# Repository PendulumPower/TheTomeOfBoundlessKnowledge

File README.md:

# The Tome Of Boundless Knowledge
A voice recognition E-paper spell tome and reference book for things such as dnd.
<br>The Tome will listen for a wake word followed by a category of spell, at which point it lists all spells in that category. When one is spoken, it will display it.
<br>I wanted to make this as an easier way to manage spells and other data for these scenerios, and plan to expand it's database past spells in the future and provide alternate firmware for purposes such as just using it as an e-reader.
Here is the full CAD model:

Front and back of the PCB:

And here is the schematic for the design:

Cost Breakdown:<br>
$35 for items in digikey BOM plus shipping, tariffs, and tax <br>
$16 for PCB with PCB, stencil, shipping, and tax <br>
$100 for e-paper display, extra cable, battery, and micro-sd card
$30 for enclosure and assembly costs (filament, more solder, and outer case materials<br>
Amazon list: <a href="https://www.amazon.com/hz/wishlist/ls/1FPKA3BWPPRNU?ref_=wl_share" target="_blank">HERE</a> <br>
Total: $181

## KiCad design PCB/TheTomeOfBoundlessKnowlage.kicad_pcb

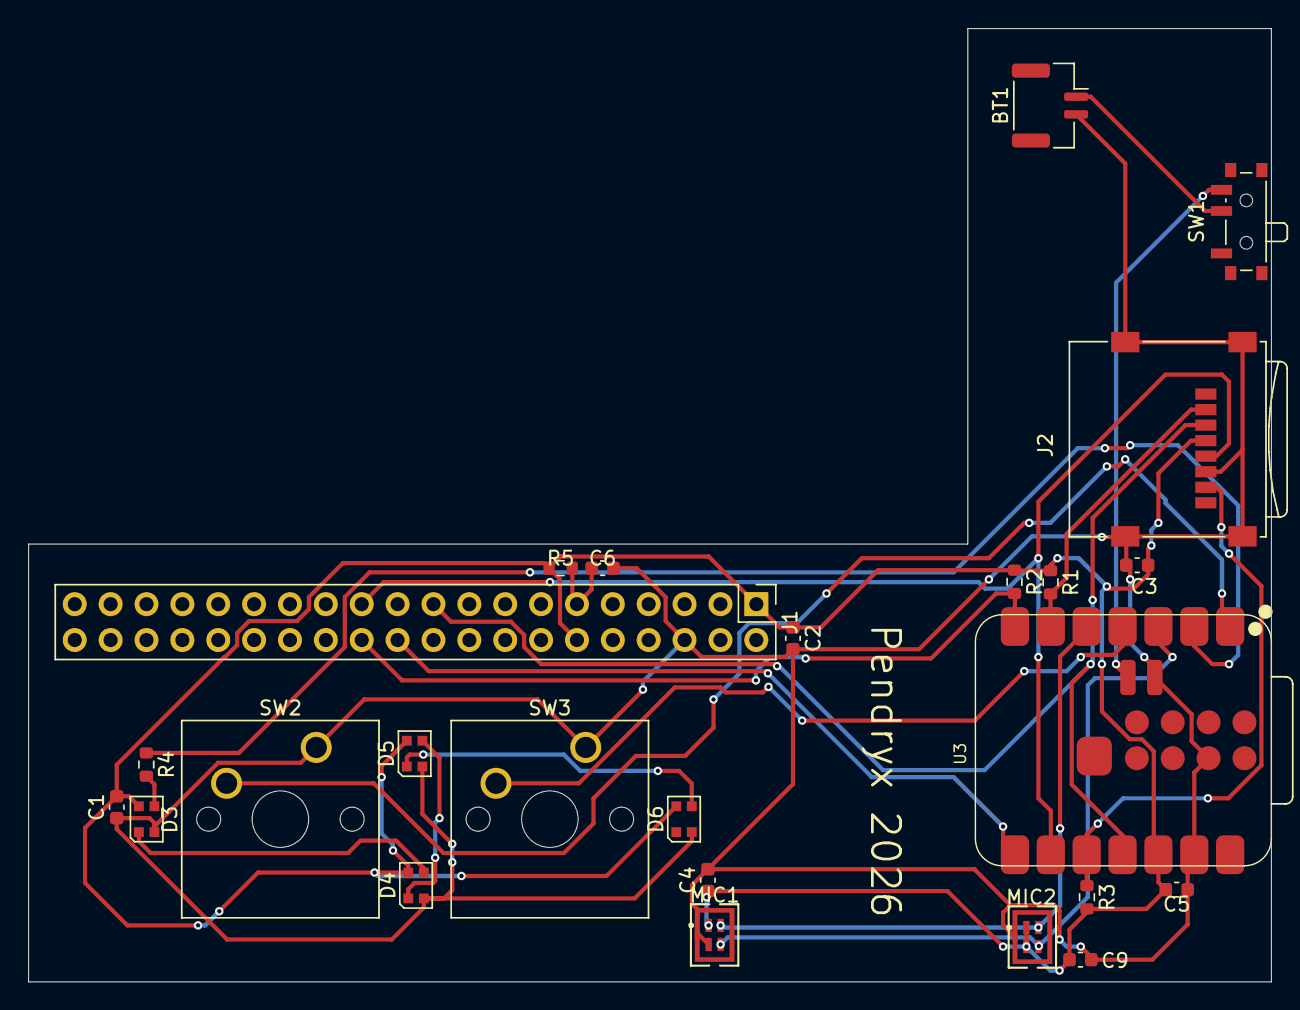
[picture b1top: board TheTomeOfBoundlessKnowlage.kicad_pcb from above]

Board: 2 copper layers, 88.0 x 67.5 mm, 25 parts (0 on the bottom side), 20 nets.

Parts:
BT1: Battery_Cell; JST_GH_SM02B-GHS-TB_1x02-1MP_P1.25mm_Horizontal
C1: 100 µF; C_0603_1608Metric
C2, C4, C9: 100nF; C_0603_1608Metric
C3, C5: 4.7 µF; C_0603_1608Metric
C6: 100 nF; C_0603_1608Metric
D3, D4, D5, D6: WS2812B-2020; LED_WS2812B-2020_PLCC4_2.0x2.0mm
J1: Conn_02x20_Odd_Even; PinHeader_2x20_P2.54mm_Vertical
J2: Micro_SD_Card; microSD_HC_Wuerth_693072010801
MIC1, MIC2: MP34DT05; HCLGA4_MP34_STM
R1, R2, R3, R5: 10 kΩ; R_0603_1608Metric
R4: 100 Ω; R_0603_1608Metric
SW1: SW_SPDT; SW_SPDT_PCM12
SW2, SW3: SW_Push; SW_Cherry_MX_1.00u_PCB
U3: XIAO-ESP32-S3-SMD

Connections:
/3.3V: C1.2, C2.1, C3.2, C4.1, C5.1, C9.1, D3.4 (VDD), D4.4 (VDD), D5.4 (VDD), D6.4 (VDD), J1.1, J1.12, J2.4 (VDD), MIC1.1 (VDD), MIC2.1 (VDD), MIC2.2 (LR), R1.1, R2.1, R3.2, R5.1, U3.12 (3V3_OUT)
/BCLK: MIC1.3 (CLK), MIC2.3 (CLK), U3.3 (D2)
/DOUT: MIC1.4 (DOUT), MIC2.4 (DOUT), U3.5 (D4)
/EPD_CS: J1.24, R2.2, U3.7 (D6)
/EPD_DC: J1.22, U3.8 (D7)
/MISO: J2.7 (DAT0), R3.1, U3.10 (D9)
/MOSI: J1.19, J2.3 (CMD), U3.11 (D10)
/SCK: J1.23, J2.5 (CLK), U3.9 (D8)
/SD_CS: J2.2 (DAT3/CD), R1.2, U3.6 (D5)
GND: BT1.2 (-), C1.1, C2.2, C3.1, C4.2, C5.2, C6.2, C9.2, D3.2 (VSS), D4.2 (VSS), D5.2 (VSS), D6.2 (VSS), J1.6, J2.6 (VSS), J2.SH (SHIELD), MIC1.2 (LR), MIC1.5 (GND), MIC2.5 (GND), SW2.1, SW3.1, U3.13 (GND), U3.18 (GND), U3.24 (GND)
unnamed: BT1.1 (+), SW1.2 (B)
unnamed: D3.3 (DIN), R4.2
unnamed: D3.1 (DOUT), D4.3 (DIN)
unnamed: D4.1 (DOUT), D5.3 (DIN)
unnamed: D5.1 (DOUT), D6.3 (DIN)
unnamed: C6.1, J1.11, R5.2
unnamed: SW1.3 (C), U3.23 (VBAT)
unnamed: SW2.2, U3.1 (D0)
unnamed: R4.1, U3.2 (D1)
unnamed: SW3.2, U3.4 (D3)
